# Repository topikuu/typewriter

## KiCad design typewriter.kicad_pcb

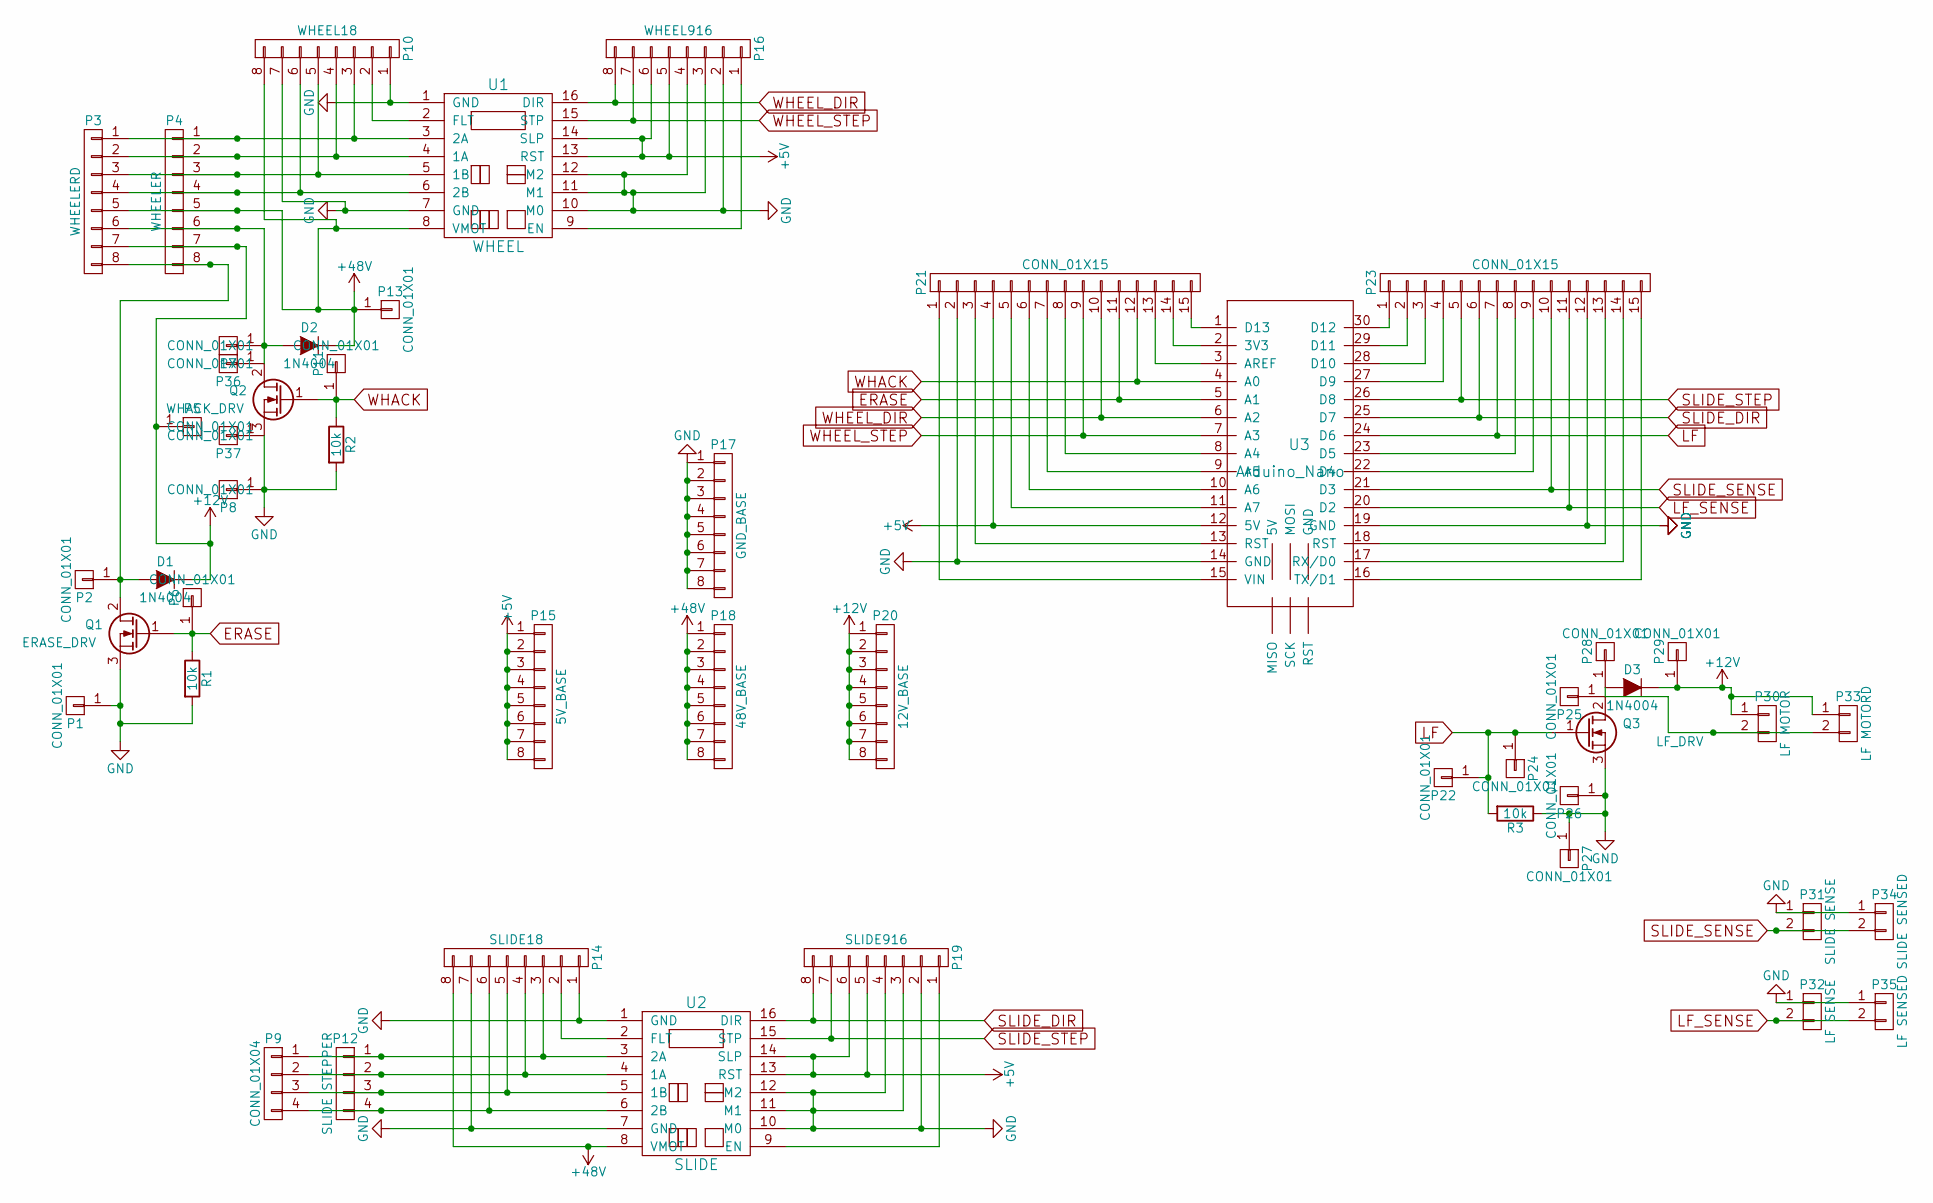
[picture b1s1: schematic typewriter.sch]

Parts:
D1, D2, D3: 1N4004; Diode_DO-41_SOD81_Horizontal_RM10
P1, P2, P5, P6, P7, P8, P11, P13, P22, P24, P25, P26, P27, P28, P29, P36, P37: CONN_01X01; Socket_Strip_Straight_1x01
P3: WHEELERD; Socket_Strip_Straight_1x08
P4: WHEELER; Socket_Strip_Straight_1x08
P9: CONN_01X04; Socket_Strip_Straight_1x04
P10: WHEEL18; Socket_Strip_Straight_1x08
P12: SLIDE STEPPER; Pin_Header_Straight_1x04
P14: SLIDE18; Socket_Strip_Straight_1x08
P15: 5V_BASE; Socket_Strip_Straight_1x08
P16: WHEEL916; Socket_Strip_Straight_1x08
P17: GND_BASE; Socket_Strip_Straight_1x08
P18: 48V_BASE; Socket_Strip_Straight_1x08
P19: SLIDE916; Socket_Strip_Straight_1x08
P20: 12V_BASE; Socket_Strip_Straight_1x08
P21, P23: CONN_01X15; Socket_Strip_Straight_1x15
P30: LF MOTOR; Pin_Header_Straight_1x02
P31: SLIDE SENSE; Pin_Header_Straight_1x02
P32: LF SENSE; Pin_Header_Straight_1x02
P33: LF MOTORD; Socket_Strip_Straight_1x02
P34: SLIDE SENSED; Socket_Strip_Straight_1x02
P35: LF SENSED; Socket_Strip_Straight_1x02
Q1: ERASE_DRV; TO-220_Neutral123_Vertical_LargePads
Q2: WHACK_DRV; TO-220_Neutral123_Vertical_LargePads
Q3: LF_DRV; TO-220_Neutral123_Vertical_LargePads
R1, R2, R3: 10k; Resistor_Horizontal_RM10mm
U1: WHEEL; Stepper_Driver_DRV8825
U2: SLIDE; Stepper_Driver_DRV8825
U3: Arduino_Nano

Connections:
+5V: P15.1, P15.2, P15.3, P15.4, P15.5, P15.6, P15.7, P15.8, P16.5, P16.6, P19.5, P19.6, P21.4, U1.13 (RST), U1.14 (SLP), U2.13 (RST), U2.14 (SLP), U3.12 (5V)
+12V: D1.1 (K), D3.1 (K), P3.7, P4.7, P5.1, P20.1, P20.2, P20.3, P20.4, P20.5, P20.6, P20.7, P20.8, P29.1, P30.1, P33.1
+48V: D2.1 (K), P3.5, P4.5, P10.8, P13.1, P14.8, P18.1, P18.2, P18.3, P18.4, P18.5, P18.6, P18.7, P18.8, U1.8 (VMOT), U2.8 (VMOT)
ERASE: P6.1, P21.11, Q1.1 (G), R1.1, U3.5 (A1)
LF: P22.1, P23.7, P24.1, Q3.1 (G), R3.2, U3.24 (D6)
LF_SENSE: P23.11, P32.2, P35.2, U3.20 (D2)
unnamed: D1.2 (A), P2.1, P3.8, P4.8, Q1.2 (D)
unnamed: D2.2 (A), P3.6, P4.6, P7.1, P36.1, Q2.2 (D)
unnamed: D3.2 (A), P25.1, P28.1, P30.2, P33.2, Q3.2 (D)
unnamed: P10.2, U1.2 (FLT)
unnamed: P3.1, P4.1, P10.3, U1.3 (2A)
unnamed: P3.3, P4.3, P10.5, U1.5 (1B)
unnamed: P3.4, P4.4, P10.6, U1.6 (2B)
unnamed: P9.1, P12.1, P14.3, U2.3 (2A)
unnamed: P9.2, P12.2, P14.4, U2.4 (1A)
unnamed: P9.3, P12.3, P14.5, U2.5 (1B)
unnamed: P9.4, P12.4, P14.6, U2.6 (2B)
unnamed: P14.2, U2.2 (FLT)
unnamed: P16.1, U1.9 (EN)
unnamed: P19.1, U2.9 (EN)
unnamed: P21.1, U3.15 (VIN)
unnamed: P21.3, U3.13 (RST)
unnamed: P21.5, U3.11 (A7)
unnamed: P21.6, U3.10 (A6)
unnamed: P21.7, U3.9 (A5)
unnamed: P21.8, U3.8 (A4)
unnamed: P21.13, U3.3 (AREF)
unnamed: P21.14, U3.2 (3V3)
unnamed: P21.15, U3.1 (D13)
unnamed: P23.1, U3.30 (D12)
unnamed: P23.2, U3.29 (D11)
unnamed: P23.3, U3.28 (D10)
unnamed: P23.4, U3.27 (D9)
unnamed: P23.8, U3.23 (D5)
unnamed: P23.9, U3.22 (D4)
unnamed: P23.13, U3.18 (RST)
unnamed: P23.14, U3.17 (RX/D0)
unnamed: P23.15, U3.16 (TX/D1)
SLIDE_DIR: P19.8, P23.6, U2.16 (DIR), U3.25 (D7)
SLIDE_SENSE: P23.10, P31.2, P34.2, U3.21 (D3)
SLIDE_STEP: P19.7, P23.5, U2.15 (STP), U3.26 (D8)
WHACK: P11.1, P21.12, Q2.1 (G), R2.1, U3.4 (A0)
WHEEL_DIR: P16.8, P21.10, U1.16 (DIR), U3.6 (A2)
WHEEL_STEP: P16.7, P21.9, U1.15 (STP), U3.7 (A3)

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
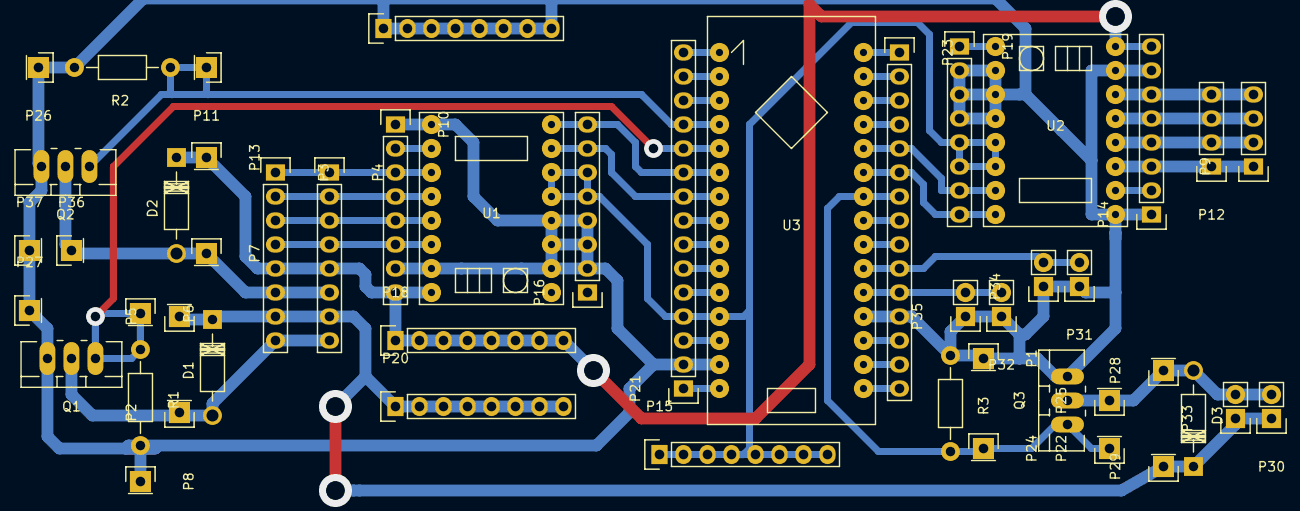
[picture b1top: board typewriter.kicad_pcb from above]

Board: 2 copper layers, 49 parts (0 on the bottom side), 46 nets.

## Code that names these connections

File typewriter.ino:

#include "libraries/SimpleStepper/SimpleStepper.h"
#include "typewriter_fwd.h"

#include <LiquidCrystal.h>

#include <stdint.h>
#include <stdlib.h>

#define DEBUG
#ifdef DEBUG
    #define debugWrite(a, b) digitalWrite(a, b)
#else
    #define debugWrite(a, b)
#endif

// Pin Declarations ------------------------------------------------------------
const int DEBUG_LED_PIN = 13;

const int LCD_RS_PIN = 5;
const int LCD_EN_PIN = 4;
const int LCD_D4_PIN = 12;
const int LCD_D5_PIN = 11;
const int LCD_D6_PIN = 10;
const int LCD_D7_PIN = 9;

const int SLIDE_DIR_PIN = 7;
const int SLIDE_STEP_PIN = 8;
const int SLIDE_SENSE_PIN = 3;
const int WHEEL_DIR_PIN = 16;
const int WHEEL_STEP_PIN = 17;
const int ERASE_PIN = 15;
const int WHACK_PIN = 14;
const int LF_MOTOR_PIN = 6;
const int LF_SENSE_PIN = 2;

// Magic numbers ---------------------------------------------------------------
const unsigned int WHACK_TIME_US = 1500;
const unsigned int LF_SENSE_DELAY_US = 100;
#ifdef DEBUG
    const unsigned long DEBUG_DISPLAY_DELAY_MS = 1000;
#endif

// Global stuff ----------------------------------------------------------------
SimpleStepper wheel(WHEEL_DIR_PIN, WHEEL_STEP_PIN, 5000);
SimpleStepper slide(SLIDE_DIR_PIN, SLIDE_STEP_PIN, 2000);
#ifdef DEBUG
    LiquidCrystal lcd(LCD_RS_PIN, LCD_EN_PIN, LCD_D4_PIN, LCD_D5_PIN, LCD_D6_PIN, LCD_D7_PIN);
#endif

// Serial control --------------------------------------------------------------
typedef void(*OpNoData)();
typedef void(*OpWithData)(uint8_t);

struct SerialCommand {
    uint8_t opcode;
    uint8_t data;
};

struct CommandData {
    const char* name;
    void* address;
    bool has_data_arg;
};

SerialCommand parseCommand(uint8_t input) {
    uint8_t opcode = (0xF0 & input) >> 4;
    uint8_t data = (0x0F & input);
    #ifdef DEBUG
        lcd.setCursor(0, 0);
        lcd.print(input);
        lcd.print(" ");
        lcd.print(opcode);
        lcd.print(" ");
        lcd.print(data);
        lcd.print("    ");
        delay(5000);
    #endif
    return {opcode, data};
}

// This is where the magic happens ---------------------------------------------
void whack() {
    debugWrite(DEBUG_LED_PIN, HIGH);
    delayMicroseconds(10*WHACK_TIME_US);
    digitalWrite(WHACK_PIN, HIGH);
    delayMicroseconds(WHACK_TIME_US);
    digitalWrite(WHACK_PIN, LOW);
    delayMicroseconds(10*WHACK_TIME_US);
    debugWrite(DEBUG_LED_PIN, LOW);
}

void linestep() {
    digitalWrite(LF_MOTOR_PIN, HIGH);
    // Wait until motor starts running
    while (!digitalRead(LF_SENSE_PIN)) {
        delayMicroseconds(LF_SENSE_DELAY_US);
    }
    // Wait for sense switch
    while (digitalRead(LF_SENSE_PIN)) {
        delayMicroseconds(LF_SENSE_DELAY_US);
    }
    digitalWrite(LF_MOTOR_PIN, LOW);
    delay(5); // FIXME: y do dis?
}

void linefeed() {
    debugWrite(DEBUG_LED_PIN, HIGH);
    linestep();
    linestep();
    debugWrite(DEBUG_LED_PIN, LOW);
}

void wheelClockwise(uint8_t num_steps) {
    debugWrite(DEBUG_LED_PIN, HIGH);
    wheel.step(int(num_steps)); // TODO: check direction
    debugWrite(DEBUG_LED_PIN, LOW);
}

void wheelCounterclockwise(uint8_t num_steps) {
    debugWrite(DEBUG_LED_PIN, HIGH);
    wheel.step(-int(num_steps)); // TODO: check direction
    debugWrite(DEBUG_LED_PIN, LOW);
}

void slideRight(uint8_t num_steps) {
    debugWrite(DEBUG_LED_PIN, HIGH);
    slide.step(int(num_steps)); // TODO: check direction
    debugWrite(DEBUG_LED_PIN, LOW);
}

void slideLeft(uint8_t num_steps) {
    debugWrite(DEBUG_LED_PIN, HIGH);
    slide.step(-int(num_steps)); // TODO: check direction
    debugWrite(DEBUG_LED_PIN, LOW);
}

void notImplemented() {
    // \:D/
}

#ifdef DEBUG
void lcd_debug_command(SerialCommand& cmd, CommandData& data) {
    //lcd.clear();
    lcd.setCursor(0, 0);
    lcd.print(data.name);
    if (data.has_data_arg) {
        lcd.print(" ");
        lcd.print(cmd.data);
    }
    lcd.print("          ");
}

void lcd_debug(const char* command, int data) {
  
}
#endif

// One of these should be called from loop() -----------------------------------
void serialControl() {
    #ifdef DEBUG
        static unsigned long last_cmd = 0;
        static const char* idle[] = { ".", "o", "O", "o" };
    #endif
    static bool requested_flag = false;
    if (Serial.available() == 0 && !requested_flag)
    {
        Serial.write(0xAA);
        requested_flag = true;
    }
    if (Serial.available() > 0)
    {
        uint8_t input = Serial.read();

        SerialCommand command = parseCommand(input);
        switch(command.opcode) {
            case 0x00:
                whack();
                break;
            case 0x01:
                linefeed();
                break;
            case 0x02:
                wheelClockwise(command.data);
                break;
            case 0x03:
                wheelCounterclockwise(command.data);
                break;
            case 0x04: // Corr up
                notImplemented();
                break;
            case 0x05: // Corr dn
                notImplemented();
                break;
            case 0x06:
                slideLeft(command.data);
                break;
            case 0x07:
                slideRight(command.data);
                break;
            case 0x08: // Carr ret
                notImplemented();
                break;
            default:
                notImplemented();
        }
        #ifdef DEBUG
            last_cmd = millis();
        #endif
        requested_flag = false;
    }
    #ifdef DEBUG
        else if (millis() > last_cmd + DEBUG_DISPLAY_DELAY_MS) {
            lcd.setCursor(0, 0);
            lcd.print(idle[(millis()/150) % 4]);
            lcd.print("               ");
        }
    #endif
}

void testall() {
    slideLeft(100);
    wheelClockwise(20);
    whack();

    delay(250);
    
    slideRight(100);
    wheelCounterclockwise(20);
    whack();

    delay(250);
/*
    slideLeft(255);
    delay(200);
    slideRight(255);
    delay(200);

    debugWrite(DEBUG_LED_PIN, HIGH);
    wheel.step(-50);
    delay(200);

    debugWrite(DEBUG_LED_PIN, LOW);
    wheel.step(50);
    delay(200);
 */
}

// Arduino functions -----------------------------------------------------------
void setup() {
    pinMode(DEBUG_LED_PIN, OUTPUT);

    pinMode(SLIDE_DIR_PIN, OUTPUT);
    pinMode(SLIDE_STEP_PIN, OUTPUT);
    pinMode(SLIDE_SENSE_PIN, OUTPUT);
    pinMode(WHEEL_DIR_PIN, OUTPUT);
    pinMode(WHEEL_STEP_PIN, OUTPUT);
    pinMode(ERASE_PIN, OUTPUT);
    pinMode(WHACK_PIN, OUTPUT);
    pinMode(LF_MOTOR_PIN, OUTPUT);
    pinMode(LF_SENSE_PIN, OUTPUT);

    // Are these redundant?
    digitalWrite(DEBUG_LED_PIN, LOW);
    digitalWrite(ERASE_PIN, LOW);
    digitalWrite(WHACK_PIN, LOW);
    digitalWrite(LF_MOTOR_PIN, LOW);

    // Steppers
    wheel.init();
    slide.init();

    #ifdef DEBUG
        lcd.begin(16, 2);
    #endif
    Serial.begin(115200);
}

void loop() {
    serialControl();
    //testall();
}

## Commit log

2016-01-23 initial
2016-01-23 Fix dependencies
2016-01-23 Reverted plain avr-gcc build back to Arduino build. Renamed Stepper -> SimpleStepper to avoid collision with Arduino stepper library. Added serial command dispatcher.
2016-02-13 Fixed whack and linefeed to active high. Adjusted delays.
2016-04-17 PCB files
2016-04-28 New pins
2016-05-04 Fixed POSIX: '\' -> '/'. Cleaned up unnecessary backups.
2016-05-04 Ditched GenericCommandDispatcher. Added optional LCD for debugging.
2016-05-04 Proof of concept python driver
2016-05-05 merkistö
2016-05-05 Host script
2016-05-05 Fixed borken stuff.
2016-05-05 Serial buffering
2016-05-05 Driver fixes.
2016-05-05 MOAR Debug in MCU.
2016-05-05 Remove function pointer pointers
